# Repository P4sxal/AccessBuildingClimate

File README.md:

This repo contains everything to build a system for monitoring temperature and humidity in a building.
Dedicated sensors are built to measure and send the data via Http API to a host server.
The collected data is stored and visualized with a web interface.

## Sensor design

The Sensor is based on the SHT30 IC from Sensiron, a digital temperature and humidity sensor.
https://sensirion.com/products/catalog/SHT30-DIS-B

A custom PCB was designed to read the sensor from a raspberry zero w.

SHT30 dongle:

## Sensor Software

The sensor is read via the I2C bus using a python script.  
The dongle features 3 status LED (red, green and orange).  
A systemd service and timer unit are logging the data as a separated, dedicated system user (mydongle).  
Data is written to a sambda drive, then copyed to local NAS an visualized using a webserver (other project).

## Usage

Copy `SHT30_software` and `setup.sh` to your Raspberry with attached dongle.  
Run `chmod +X setup.sh`, then `sudo ./setup.sh` to finish installation.
The device will start logging climatic data.  
Verify the running service:  
`systemctl status mydongle.service` or `systemctl status mydongle.timer`  

```
{"time": "Mon Feb 24 11:22:41 2025", "temperature": 14.16, "humidity": 59.68, "timestamp": 1740392561.3886838, "hostname": "cellar"}
```
That's it.

---
written by P4sxal 2024-2025

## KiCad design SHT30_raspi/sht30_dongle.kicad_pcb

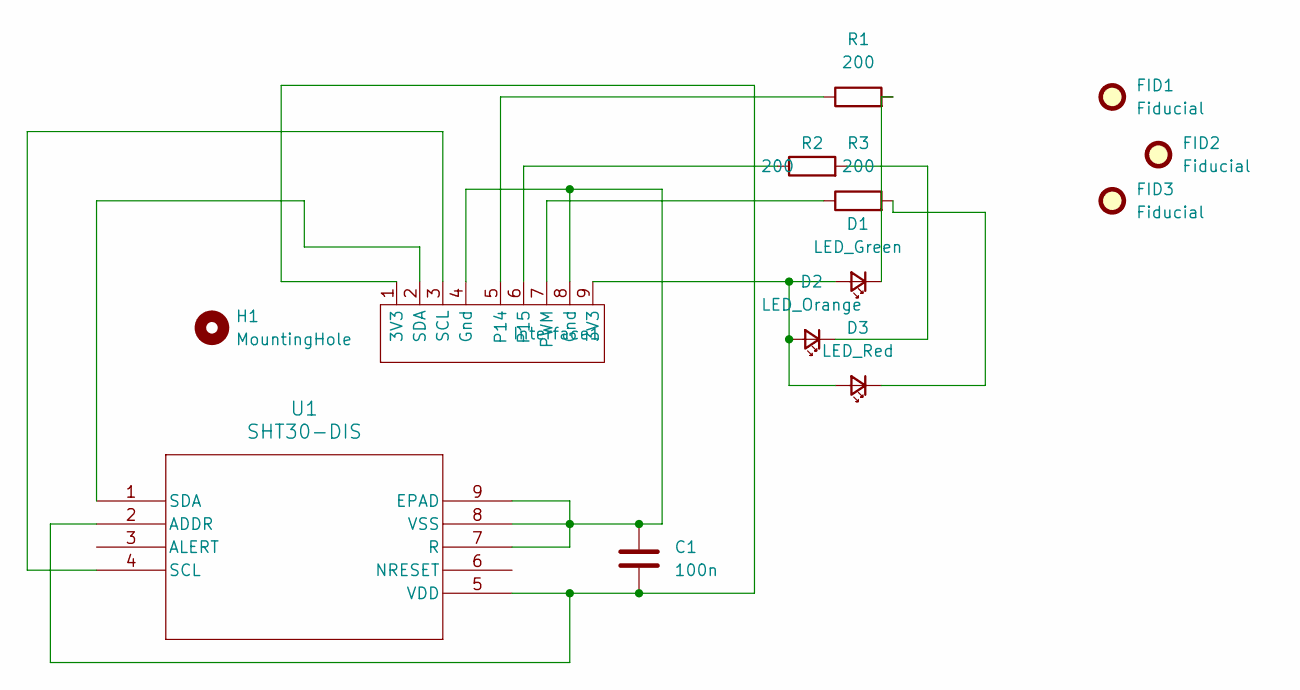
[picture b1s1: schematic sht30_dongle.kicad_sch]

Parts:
C1: 100n; C_0402_1005Metric
D1: LED_Green; LED_0402_1005Metric
D2: LED_Orange; LED_0402_1005Metric
D3: LED_Red; LED_0402_1005Metric
FID1, FID2, FID3: Fiducial; Fiducial_0.5mm_Mask1mm
H1: MountingHole; MountingHole_2.7mm_M2.5
Interface1: Pi_i2c_interface
R1, R2, R3: 200; LED_0402_1005Metric
U1: SHT30-DIS; SHT3X_DIS_SEN

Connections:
unnamed: D1.2 (A), D2.2 (A), D3.2 (A), Interface1.9 (3V3)
unnamed: D1.1 (K), R1.2
unnamed: D2.1 (K), R2.2
unnamed: D3.1 (K), R3.2
unnamed: Interface1.5 (P14), R1.1
unnamed: Interface1.6 (P15), R2.1
unnamed: Interface1.7 (PWM), R3.1
unnamed: Interface1.3 (SCL), U1.4 (SCL)
unnamed: Interface1.2 (SDA), U1.1 (SDA)
unnamed: C1.2, Interface1.1 (3V3), U1.2 (ADDR), U1.5 (VDD)
unnamed: C1.1, Interface1.4 (Gnd), Interface1.8 (Gnd), U1.7 (R), U1.8 (VSS), U1.9 (EPAD)

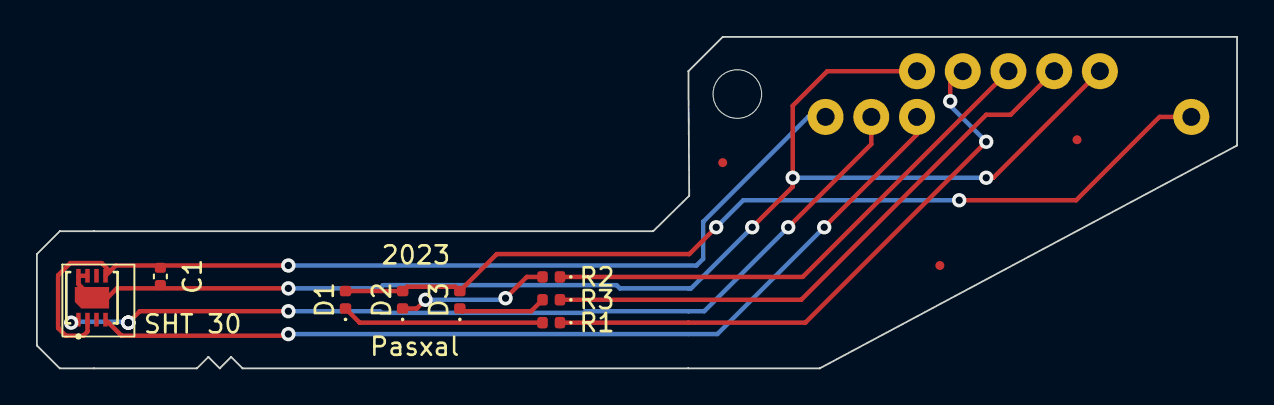
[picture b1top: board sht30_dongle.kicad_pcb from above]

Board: 2 copper layers, 66.7 x 18.4 mm, 13 parts (0 on the bottom side), 11 nets.

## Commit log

2024-10-01 initial test
2024-10-01 Dongle_pics
2024-10-20 start cleaning
2024-11-13 structure cleaned
2024-11-13 Update README.md
    picture added
2025-02-10 service added, no crontab needed
2025-02-10 Update README.md
    New pictures
2025-02-15 systemd service and timer written
2025-02-26 systemd service and timer added and tested successfully
2025-02-26 Update README.md
    Description and Usage added
2025-02-26 gitignore update
2025-02-26 gitignore update2
2025-02-26 data removed
2025-02-26 data removed2
2025-03-15 setup.sh updated and tested
